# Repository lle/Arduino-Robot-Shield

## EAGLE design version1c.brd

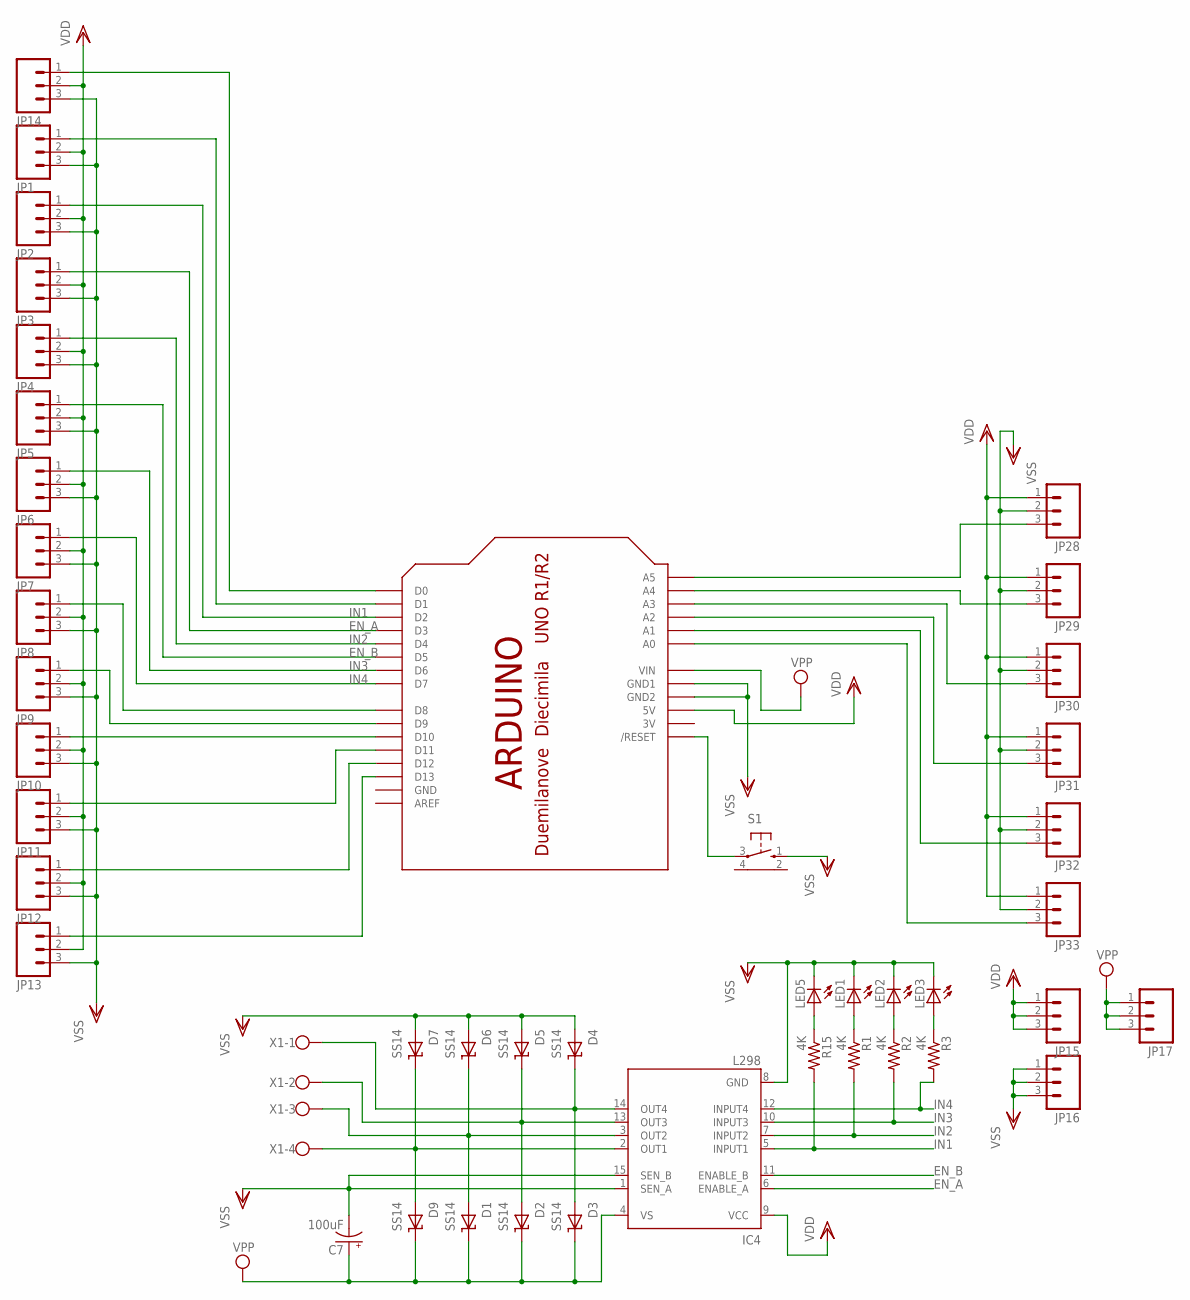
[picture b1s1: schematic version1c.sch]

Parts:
C7: 100uF; 153CLV-0605
D1, D2, D3, D4, D5, D6, D7, D9: SS14; SMA
IC4: L298; MULTIWATT-15
JP1, JP2, JP3, JP4, JP5, JP6, JP7, JP8, JP9, JP10, JP11, JP12, JP13, JP14, JP15, JP16, JP17, JP28, JP29, JP30, JP31, JP32, JP33: M03PTH; 1X03
LED1, LED2, LED3, LED5: LEDCHIP-LED0805; CHIP-LED0805
R1, R2, R3, R15: 4K; R0805
S1: 10-XX-RPAD; B3F-10XX-RPAD
U$1: ARDUINO-NOHOLE
X1: W237-4

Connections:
3V: U$1.3V
EN_A: IC4.6 (ENABLE_A), JP3.1, U$1.D3
EN_B: IC4.11 (ENABLE_B), JP5.1, U$1.D5
GND: U$1.GND
IN1: IC4.5 (INPUT1), JP2.1, R15.2, U$1.D2
IN2: IC4.7 (INPUT2), JP4.1, R1.2, U$1.D4
IN3: IC4.10 (INPUT3), JP6.1, R2.2, U$1.D6
IN4: IC4.12 (INPUT4), JP7.1, R3.2, U$1.D7
unnamed: JP13.1, U$1.D13
unnamed: JP12.1, U$1.D12
unnamed: JP28.3, U$1.A5
unnamed: JP11.1, U$1.D11
unnamed: JP10.1, U$1.D10
unnamed: JP29.3, U$1.A4
unnamed: JP9.1, U$1.D9
unnamed: JP8.1, U$1.D8
unnamed: JP30.3, U$1.A3
unnamed: LED3.A, R3.1
unnamed: LED2.A, R2.1
unnamed: JP31.3, U$1.A2
unnamed: LED1.A, R1.1
unnamed: LED5.A, R15.1
unnamed: JP33.3, U$1.A0
unnamed: JP32.3, U$1.A1
unnamed: JP1.1, U$1.D1
unnamed: JP14.1, U$1.D0
unnamed: S1.3, U$1.RESET (/RESET)
unnamed: D7.P$1 (K), D9.P$2 (A), IC4.2 (OUT1), X1.4
unnamed: D1.P$2 (A), D6.P$1 (K), IC4.3 (OUT2), X1.3
unnamed: D2.P$2 (A), D5.P$1 (K), IC4.13 (OUT3), X1.2
unnamed: D3.P$2 (A), D4.P$1 (K), IC4.14 (OUT4), X1.1
VDD: IC4.9 (VCC), JP1.2, JP2.2, JP3.2, JP4.2, JP5.2, JP6.2, JP7.2, JP8.2, JP9.2, JP10.2, JP11.2, JP12.2, JP13.2, JP14.2, JP15.1, JP15.2, JP15.3, JP28.1, JP29.1, JP30.1, JP31.1, JP32.1, JP33.1, U$1.5V
VPP: C7.+, D1.P$1 (K), D2.P$1 (K), D3.P$1 (K), D9.P$1 (K), IC4.4 (VS), JP17.1, JP17.2, JP17.3, U$1.VIN
VSS: C7.-, D4.P$2 (A), D5.P$2 (A), D6.P$2 (A), D7.P$2 (A), IC4.1 (SEN_A), IC4.8 (GND), IC4.15 (SEN_B), JP1.3, JP2.3, JP3.3, JP4.3, JP5.3, JP6.3, JP7.3, JP8.3, JP9.3, JP10.3, JP11.3, JP12.3, JP13.3, JP14.3, JP16.1, JP16.2, JP16.3, JP28.2, JP29.2, JP30.2, JP31.2, JP32.2, JP33.2, LED1.C, LED2.C, LED3.C, LED5.C, S1.1 (S), U$1.GND1, U$1.GND2

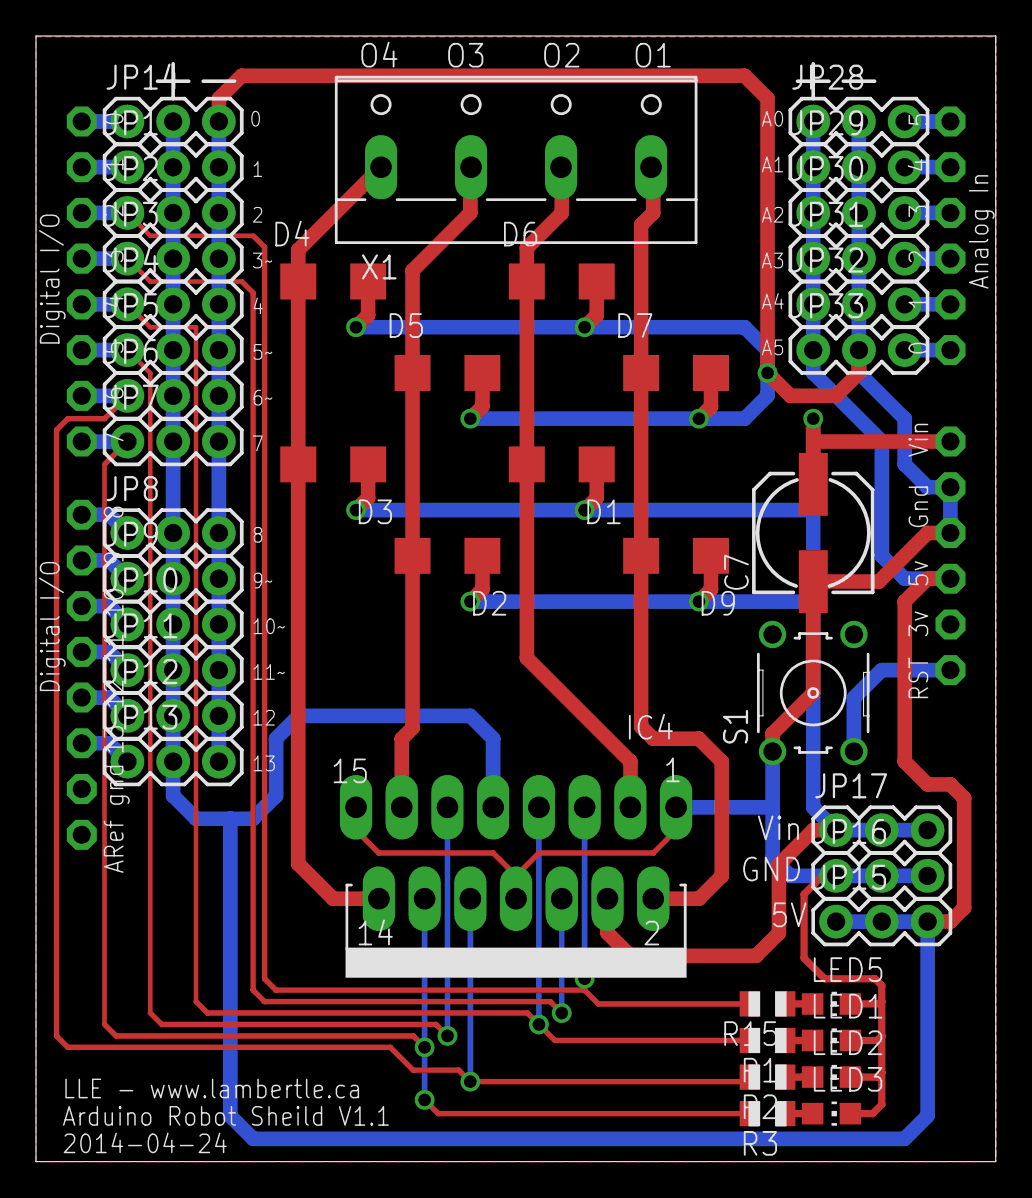
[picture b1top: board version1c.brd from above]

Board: 2 copper layers, 53.3 x 62.5 mm, 44 parts (0 on the bottom side), 32 nets.

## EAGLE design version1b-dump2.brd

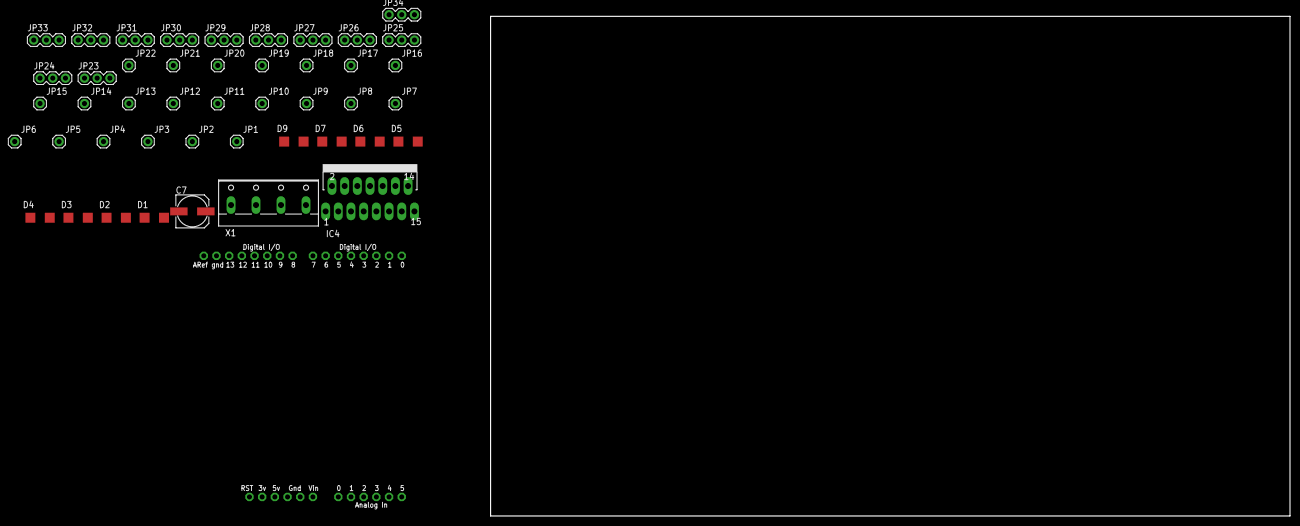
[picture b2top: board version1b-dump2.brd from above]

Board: 2 copper layers, 160.0 x 100.0 mm, 46 parts (0 on the bottom side), 38 nets, no tracks yet.

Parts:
C7: 100uF; 153CLV-0605
D1, D2, D3, D4, D5, D6, D7, D9: SS14; SMA
IC4: L298; MULTIWATT-15
JP1, JP2, JP3, JP4, JP5, JP6, JP7, JP8, JP9, JP10, JP11, JP12, JP13, JP14, JP15, JP16, JP17, JP18, JP19, JP20, JP21, JP22: M01PTH; 1X01
JP23, JP24, JP25, JP26, JP27, JP28, JP29, JP30, JP31, JP32, JP33, JP34: 1X03
U$1: ARDUINO-NOHOLE
X1: W237-4

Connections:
unnamed: JP1.1, U$1.D0
unnamed: JP2.1, U$1.D1
unnamed: JP28.3, U$1.A5
unnamed: JP3.1, U$1.D2
unnamed: JP4.1, U$1.D4
unnamed: JP29.3, U$1.A4
unnamed: JP5.1, U$1.D7
unnamed: JP6.1, U$1.D8
unnamed: JP30.3, U$1.A3
unnamed: JP7.1, U$1.D12
unnamed: JP8.1, U$1.D13
unnamed: JP31.3, U$1.A2
unnamed: JP9.1, U$1.GND
unnamed: JP23.1, U$1.D3
unnamed: JP24.1, U$1.D5
unnamed: JP33.3, U$1.A0
unnamed: JP32.3, U$1.A1
unnamed: JP10.1, U$1.AREF
unnamed: JP14.1, U$1.RESET
unnamed: JP25.1, U$1.D6
unnamed: JP15.1, U$1.3V
unnamed: JP16.1, U$1.GND1
unnamed: JP27.1, U$1.D10
unnamed: D7.P$1, D9.P$2, IC4.2, X1.4
unnamed: D1.P$2, D6.P$1, IC4.3, X1.3
unnamed: JP34.1, U$1.D11
unnamed: D2.P$2, D5.P$1, IC4.13, X1.2
unnamed: D3.P$2, D4.P$1, IC4.14, X1.1
unnamed: IC4.6, JP22.1
unnamed: JP26.1, U$1.D9
unnamed: IC4.11, JP21.1
unnamed: IC4.12, JP17.1
unnamed: IC4.10, JP18.1
unnamed: IC4.7, JP19.1
unnamed: IC4.5, JP20.1
VDD: IC4.9, JP13.1, JP23.2, JP24.2, JP25.2, JP26.2, JP27.2, JP28.1, JP29.1, JP30.1, JP31.1, JP32.1, JP33.1, JP34.2, U$1.5V
VPP: C7.+, D1.P$1, D2.P$1, D3.P$1, D9.P$1, IC4.4, JP11.1, U$1.VIN
VSS: C7.-, D4.P$2, D5.P$2, D6.P$2, D7.P$2, IC4.1, IC4.8, IC4.15, JP12.1, JP23.3, JP24.3, JP25.3, JP26.3, JP27.3, JP28.2, JP29.2, JP30.2, JP31.2, JP32.2, JP33.2, JP34.3, U$1.GND2

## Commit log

2014-04-19 Edited old 2013 version
    Now with LED indicator
    surface mount diodes and resistors
2014-05-17 Version 1c Created
    Added debug LED and surface mount components

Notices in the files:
parts and their libraries:
SparkFun: Licensing: CC v3.0 Share-Alike You are welcome to use this library for commercial purposes.
